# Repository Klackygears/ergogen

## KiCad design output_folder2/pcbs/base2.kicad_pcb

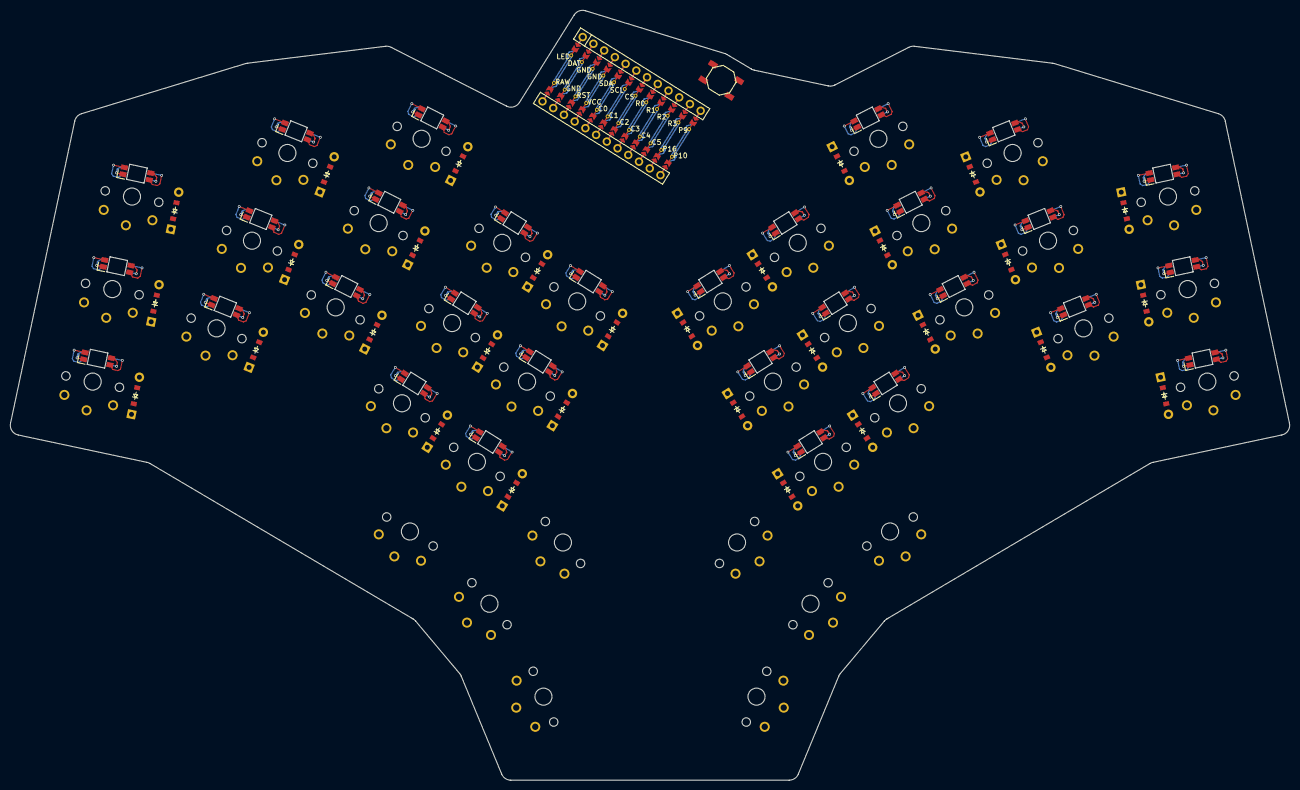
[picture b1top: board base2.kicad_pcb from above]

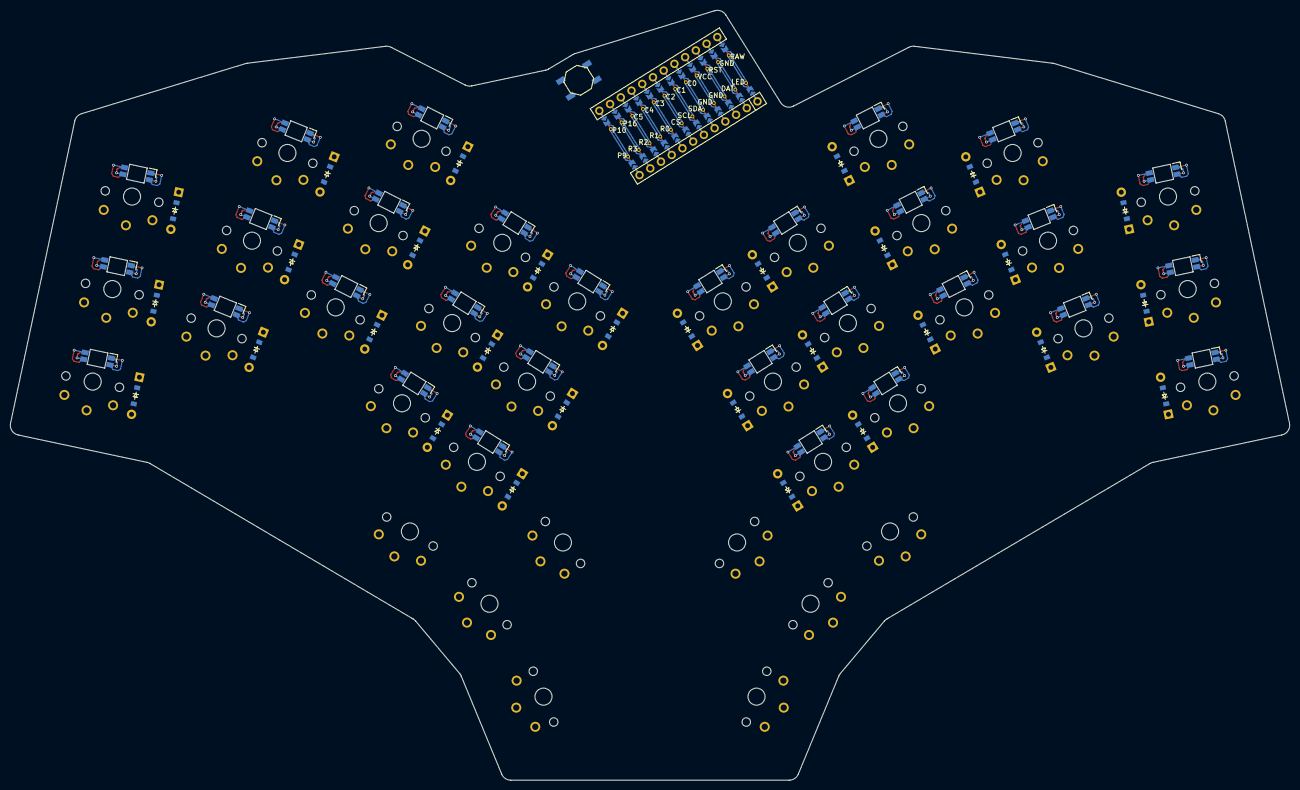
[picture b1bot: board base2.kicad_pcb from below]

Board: 2 copper layers, 257.0 x 154.6 mm, 101 parts (30 on the bottom side), 51 nets.

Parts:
B1, B2: SW_TACT_ALPS_SKQGABE010
D1, D2, D3, D4, D5, D6, D7, D8, D9, D10, D11, D12, D13, D14, D15, D16, D17, D18, D19, D20, D21, D22, D23, D24, D25, D26, D27, D28, D29, D30: ComboDiode
LED1, LED2, LED3, LED4, LED5, LED6, LED7, LED8, LED9, LED10, LED11, LED12, LED13, LED14, LED15, LED16, LED17, LED18, LED19, LED20, LED21, LED22, LED23, LED24, LED25, LED26, LED27, LED28, LED29, LED30: YS-SK6812MINI-E (per-key, reversible)
MCU1: nice_nano
S1, S2, S3, S4, S5, S6, S7, S8, S9, S10, S11, S12, S13, S14, S15, S16, S17, S18, S19, S20, S21, S22, S23, S24, S25, S26, S27, S28, S29, S30, S31, S32, S33, S34, S35, S36, S37, S38: PG1350

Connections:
C0: MCU1.5, S23.1, S24.1, S25.1
C1: MCU1.6, S26.1, S27.1, S28.1
C2: MCU1.7, S29.1, S30.1, S31.1
C3: MCU1.8, S32.1, S33.1, S34.1
C4: MCU1.9, S35.1
C5: MCU1.10, S36.1
CS: MCU1.118, S10.1, S11.1, S12.1, S18.1
DAT: MCU1.123, S1.1, S2.1, S3.1
GND: B1.1, B2.1, LED1.3, LED2.3, LED3.3, LED4.3, LED5.3, LED6.3, LED7.3, LED8.3, LED9.3, LED10.3, LED11.3, LED12.3, LED13.3, LED14.3, LED15.3, LED16.3, LED17.3, LED18.3, LED19.3, LED20.3, LED21.3, LED22.3, LED23.3, LED24.3, LED25.3, LED26.3, LED27.3, LED28.3, LED29.3, LED30.3, MCU1.2, MCU1.121, MCU1.122
P10: MCU1.12, S20.1, S21.1, S22.1, S38.1
P16: MCU1.11, S37.1
R0: MCU1.117, S13.1, S14.1, S15.1, S19.1
R1: D1.1, D4.1, D7.1, D10.1, D13.1, D16.1, D19.1, D22.1, D25.1, D28.1, MCU1.116
R2: D2.1, D5.1, D8.1, D11.1, D14.1, D17.1, D20.1, D23.1, D26.1, D29.1, MCU1.115
R3: D3.1, D6.1, D9.1, D12.1, D15.1, D18.1, D21.1, D24.1, D27.1, D30.1, MCU1.114
RST: B1.2, B2.2, MCU1.3
SDA: MCU1.120, S4.1, S5.1, S6.1, S16.1
SLC: S7.1, S8.1, S9.1, S17.1
VCC: LED1.1, LED2.1, LED3.1, LED4.1, LED5.1, LED6.1, LED7.1, LED8.1, LED9.1, LED10.1, LED11.1, LED12.1, LED13.1, LED14.1, LED15.1, LED16.1, LED17.1, LED18.1, LED19.1, LED20.1, LED21.1, LED22.1, LED23.1, LED24.1, LED25.1, LED26.1, LED27.1, LED28.1, LED29.1, LED30.1, MCU1.4
home_thumb: S17.2, S19.2
index_bottom: D10.2, S10.2
index_home: D11.2, S11.2
index_top: D12.2, S12.2
inner_bottom: D13.2, S13.2
inner_home: D14.2, S14.2
inner_top: D15.2, S15.2
middle_bottom: D7.2, S7.2
middle_home: D8.2, S8.2
middle_top: D9.2, S9.2
mirror_home_thumb: S36.2, S38.2
mirror_index_bottom: D25.2, S29.2
mirror_index_home: D26.2, S30.2
mirror_index_top: D27.2, S31.2
mirror_inner_bottom: D28.2, S32.2
mirror_inner_home: D29.2, S33.2
mirror_inner_top: D30.2, S34.2
mirror_middle_bottom: D22.2, S26.2
mirror_middle_home: D23.2, S27.2
mirror_middle_top: D24.2, S28.2
mirror_pinky_bottom: D16.2, S20.2
mirror_pinky_home: D17.2, S21.2
mirror_pinky_top: D18.2, S22.2
mirror_ring_bottom: D19.2, S23.2
mirror_ring_home: D20.2, S24.2
mirror_ring_top: D21.2, S25.2
pinky_bottom: D1.2, S1.2
pinky_home: D2.2, S2.2
pinky_top: D3.2, S3.2
ring_bottom: D4.2, S4.2
ring_home: D5.2, S5.2
ring_top: D6.2, S6.2
